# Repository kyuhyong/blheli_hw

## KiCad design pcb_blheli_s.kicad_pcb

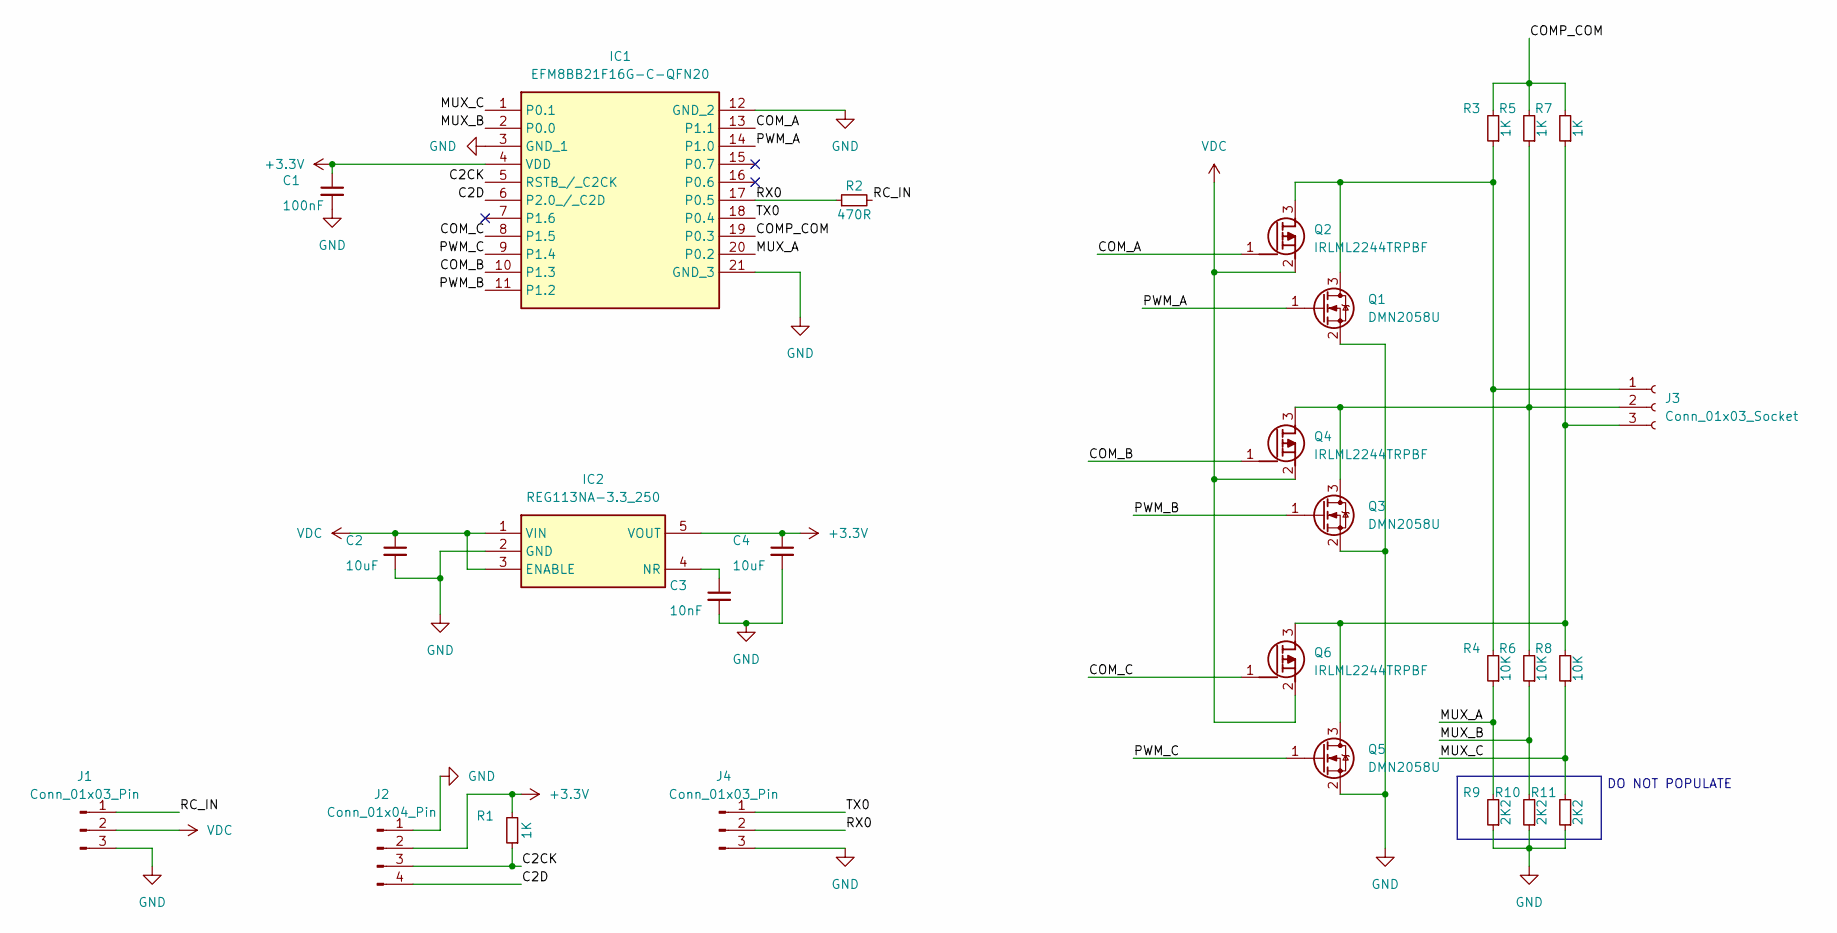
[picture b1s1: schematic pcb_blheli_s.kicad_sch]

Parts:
C1: 100nF; C_0603_1608Metric
C2, C4: 10uF; C_0603_1608Metric
C3: 10nF; C_0603_1608Metric
IC1: EFM8BB21F16G-C-QFN20; CP2102NA02GQFN20; Mouser Part Number 634-8BB21F16GCQFN20
IC2: REG113NA-3.3_250; SOT95P280X145-5N; Mouser Part Number 595-REG113NA-3.3/250
J1: Conn_01x03_Pin; HEADER_1x03_2.54mm_CASTELLATED
J2: Conn_01x04_Pin; PinHeader_1x04_P1.27mm_Vertical
J3: Conn_01x03_Socket; PinHeader_1x03_P2.00mm_Vertical
J4: Conn_01x03_Pin; PinHeader_1x03_P2.00mm_Vertical
Q1, Q3, Q5: DMN2058U; SOT-23
Q2, Q4, Q6: IRLML2244TRPBF; SOT95P237X112-3N; Mouser Part Number 942-IRLML2244TRPBF
R1, R3, R5, R7: 1K; R_0603_1608Metric
R2: 470R; R_0603_1608Metric
R4, R6, R8: 10K; R_0603_1608Metric
R9, R10, R11: 2K2; R_0603_1608Metric

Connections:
+3.3V: C1.1, C4.1, IC1.4 (VDD), IC2.5 (VOUT), J2.2, R1.2
/C2CK: IC1.5 (RSTB_/_C2CK), J2.3, R1.1
/C2D: IC1.6 (P2.0_/_C2D), J2.4
/COMP_COM: IC1.19 (P0.3), R3.2, R5.2, R7.2
/COM_A: IC1.13 (P1.1), Q2.1 (G)
/COM_B: IC1.10 (P1.3), Q4.1 (G)
/COM_C: IC1.8 (P1.5), Q6.1 (G)
/MUX_A: IC1.20 (P0.2), R4.1, R9.2
/MUX_B: IC1.2 (P0.0), R6.1, R10.2
/MUX_C: IC1.1 (P0.1), R8.1, R11.2
/PWM_A: IC1.14 (P1.0), Q1.1 (G)
/PWM_B: IC1.11 (P1.2), Q3.1 (G)
/PWM_C: IC1.9 (P1.4), Q5.1 (G)
/RC_IN: J1.1, R2.2
/RX0: IC1.17 (P0.5), J4.2, R2.1
/TX0: IC1.18 (P0.4), J4.1
GND: C1.2, C2.2, C3.2, C4.2, IC1.3 (GND_1), IC1.12 (GND_2), IC1.21 (GND_3), IC2.2 (GND), J1.3, J2.1, J4.3, Q1.2 (S), Q3.2 (S), Q5.2 (S), R9.1, R10.1, R11.1
unnamed: C3.1, IC2.4 (NR)
unnamed: J3.1, Q1.3 (D), Q2.3 (D), R3.1, R4.2
unnamed: J3.2, Q3.3 (D), Q4.3 (D), R5.1, R6.2
unnamed: J3.3, Q5.3 (D), Q6.3 (D), R7.1, R8.2
VDC: C2.1, IC2.1 (VIN), IC2.3 (ENABLE), J1.2, Q2.2 (S), Q4.2 (S), Q6.2 (S)

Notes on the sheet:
DO NOT POPULATE

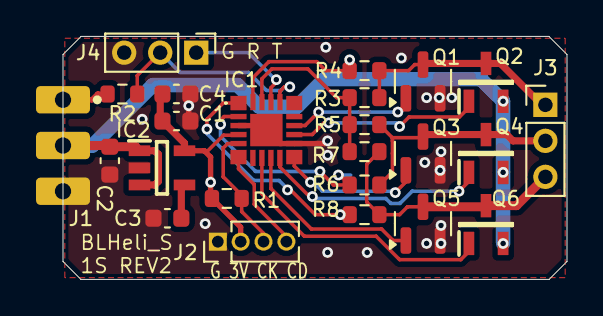
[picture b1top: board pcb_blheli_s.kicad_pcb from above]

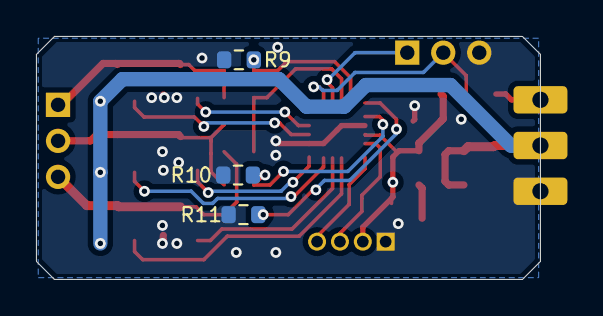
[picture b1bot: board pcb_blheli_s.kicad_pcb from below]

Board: 2 copper layers, 28.0 x 13.5 mm, 27 parts (3 on the bottom side), 22 nets.

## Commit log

2024-08-05 Finished gerber
2024-08-20 Updated schematics
2024-08-20 Updated gerber
2024-08-22 Ordered rev2
